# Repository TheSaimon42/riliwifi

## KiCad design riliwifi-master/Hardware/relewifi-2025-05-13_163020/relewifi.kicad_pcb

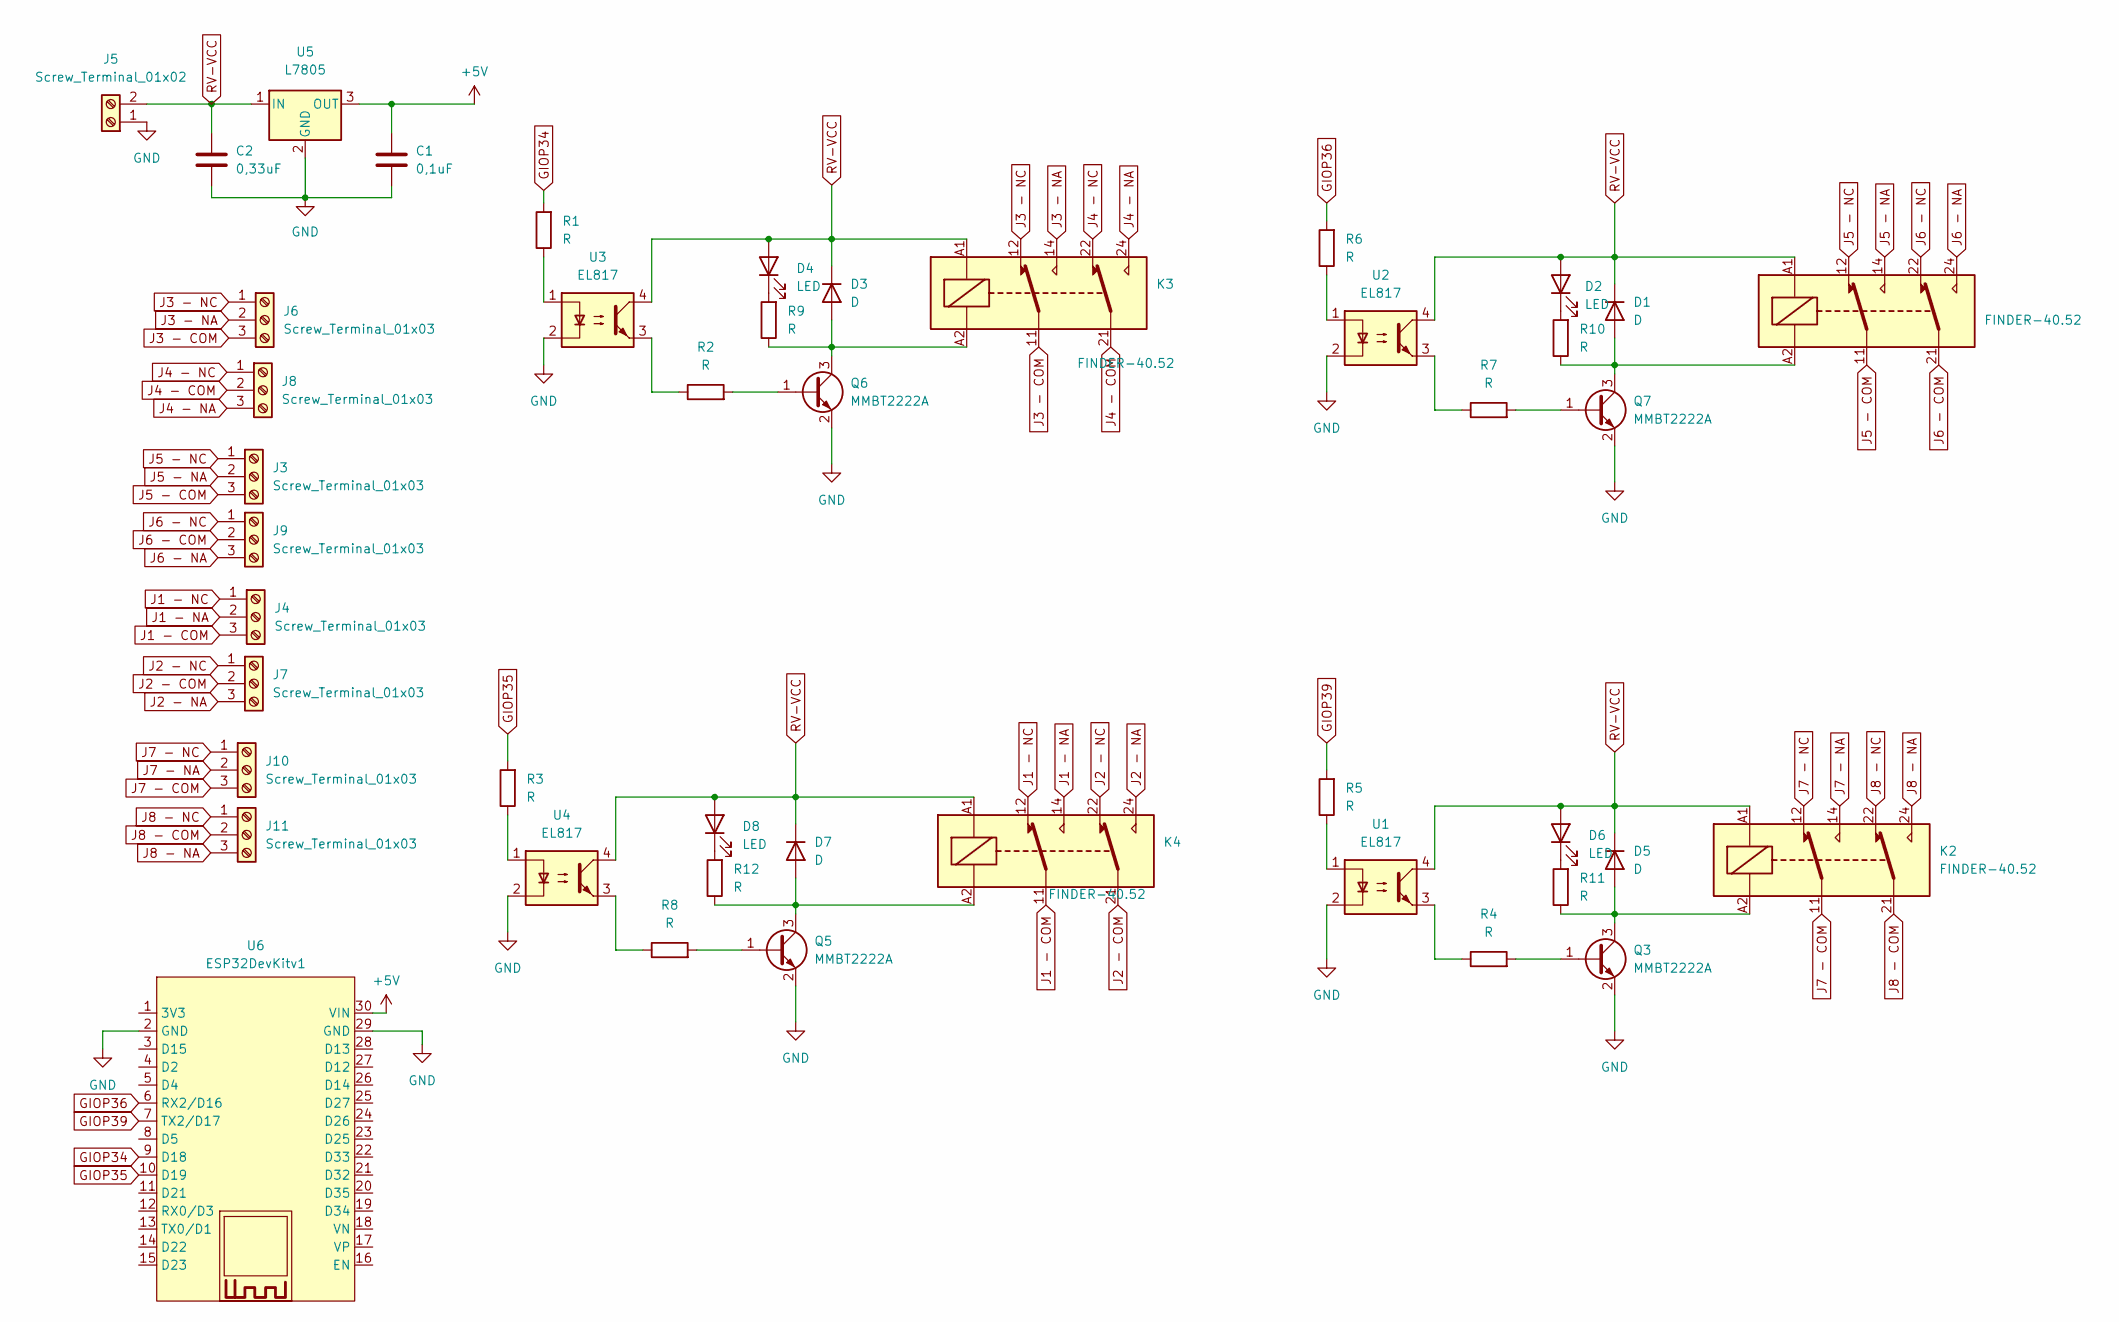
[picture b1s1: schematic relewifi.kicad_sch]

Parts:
C1: 0,1uF; C_Axial_L3.8mm_D2.6mm_P7.50mm_Horizontal
C2: 0,33uF; C_Axial_L3.8mm_D2.6mm_P7.50mm_Horizontal
D1, D3, D5, D7: D; D_SMA
D2, D4, D6, D8: LED; LED_D5.0mm_Clear
J3, J4, J6, J7, J8, J9, J10, J11: Screw_Terminal_01x03; TerminalBlock_Xinya_XY308-2.54-3P_1x03_P2.54mm_Horizontal
J5: Screw_Terminal_01x02; TerminalBlock_bornier-2_P5.08mm
K1, K2, K3, K4: FINDER-40.52; Relay_DPDT_Finder_40.52
Q3, Q5, Q6, Q7: MMBT2222A; SOT-23
R1, R2, R3, R4, R5, R6, R7, R8, R9, R10, R11, R12: R; R_0805_2012Metric
U1, U2, U3, U4: EL817; DIP-4_W7.62mm
U5: L7805; TO-220-3_Vertical
U6: ESP32DevKitv1; ESP32-C3-DevKitM-1

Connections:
+5V: C1.1, U5.3 (OUT), U6.30 (VIN)
GIOP34: R1.2, U6.9 (D18)
GIOP35: R3.2, U6.10 (D19)
GIOP36: R6.2, U6.6 (RX2/D16)
GIOP39: R5.2, U6.7 (TX2/D17)
GND: C1.2, C2.2, J5.1, Q3.2 (E), Q5.2 (E), Q6.2 (E), Q7.2 (E), U1.2, U2.2, U3.2, U4.2, U5.2 (GND), U6.2 (GND), U6.29 (GND)
J1 - COM: J4.3, K4.11
J1 - NA: J4.2, K4.14
J1 - NC: J4.1, K4.12
J2 - COM: J7.2, K4.21
J2 - NA: J7.3, K4.24
J2 - NC: J7.1, K4.22
J3 - COM: J6.3, K3.11
J3 - NA: J6.2, K3.14
J3 - NC: J6.1, K3.12
J4 - COM: J8.2, K3.21
J4 - NA: J8.3, K3.24
J4 - NC: J8.1, K3.22
J5 - COM: J3.3, K1.11
J5 - NA: J3.2, K1.14
J5 - NC: J3.1, K1.12
J6 - COM: J9.2, K1.21
J6 - NA: J9.3, K1.24
J6 - NC: J9.1, K1.22
J7 - COM: J10.3, K2.11
J7 - NA: J10.2, K2.14
J7 - NC: J10.1, K2.12
J8 - COM: J11.2, K2.21
J8 - NA: J11.3, K2.24
J8 - NC: J11.1, K2.22
unnamed: D1.2 (A), K1.A2, Q7.3 (C), R10.1
unnamed: D2.1 (K), R10.2
unnamed: D3.2 (A), K3.A2, Q6.3 (C), R9.1
unnamed: D4.1 (K), R9.2
unnamed: D5.2 (A), K2.A2, Q3.3 (C), R11.1
unnamed: D6.1 (K), R11.2
unnamed: D7.2 (A), K4.A2, Q5.3 (C), R12.1
unnamed: D8.1 (K), R12.2
unnamed: Q3.1 (B), R4.2
unnamed: Q5.1 (B), R8.2
unnamed: Q6.1 (B), R2.2
unnamed: Q7.1 (B), R7.2
unnamed: R1.1, U3.1
unnamed: R2.1, U3.3
unnamed: R3.1, U4.1
unnamed: R4.1, U1.3
unnamed: R5.1, U1.1
unnamed: R6.1, U2.1
unnamed: R7.1, U2.3
unnamed: R8.1, U4.3
RV-VCC: C2.1, D1.1 (K), D2.2 (A), D3.1 (K), D4.2 (A), D5.1 (K), D6.2 (A), D7.1 (K), D8.2 (A), J5.2, K1.A1, K2.A1, K3.A1, K4.A1, U1.4, U2.4, U3.4, U4.4, U5.1 (IN)

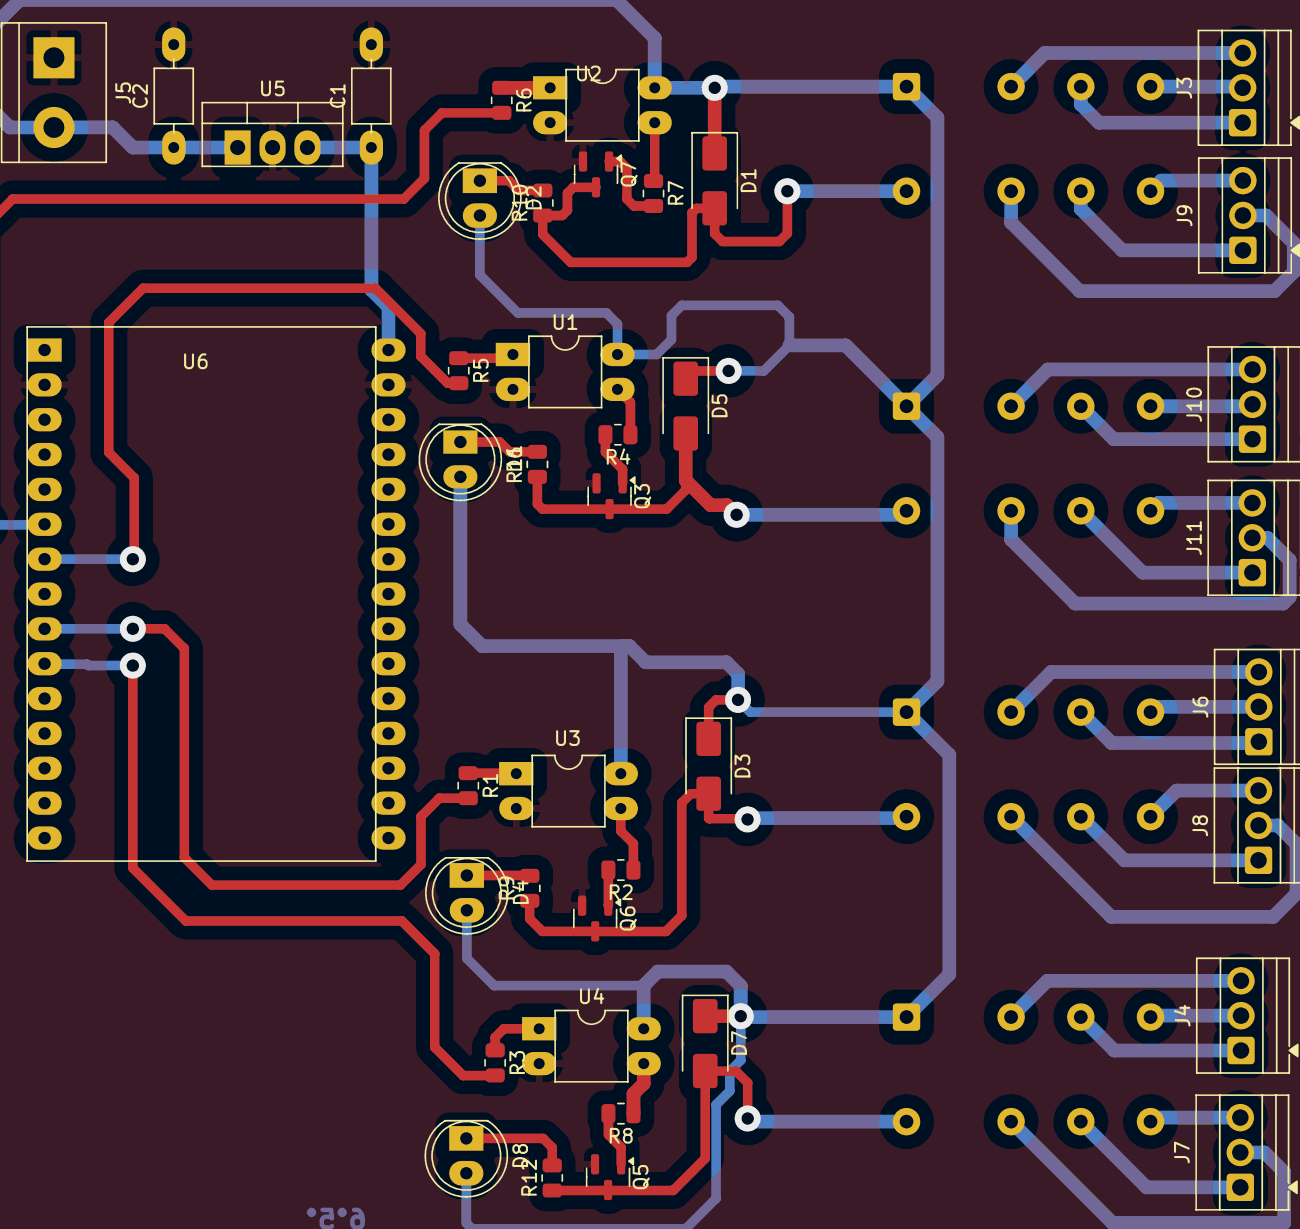
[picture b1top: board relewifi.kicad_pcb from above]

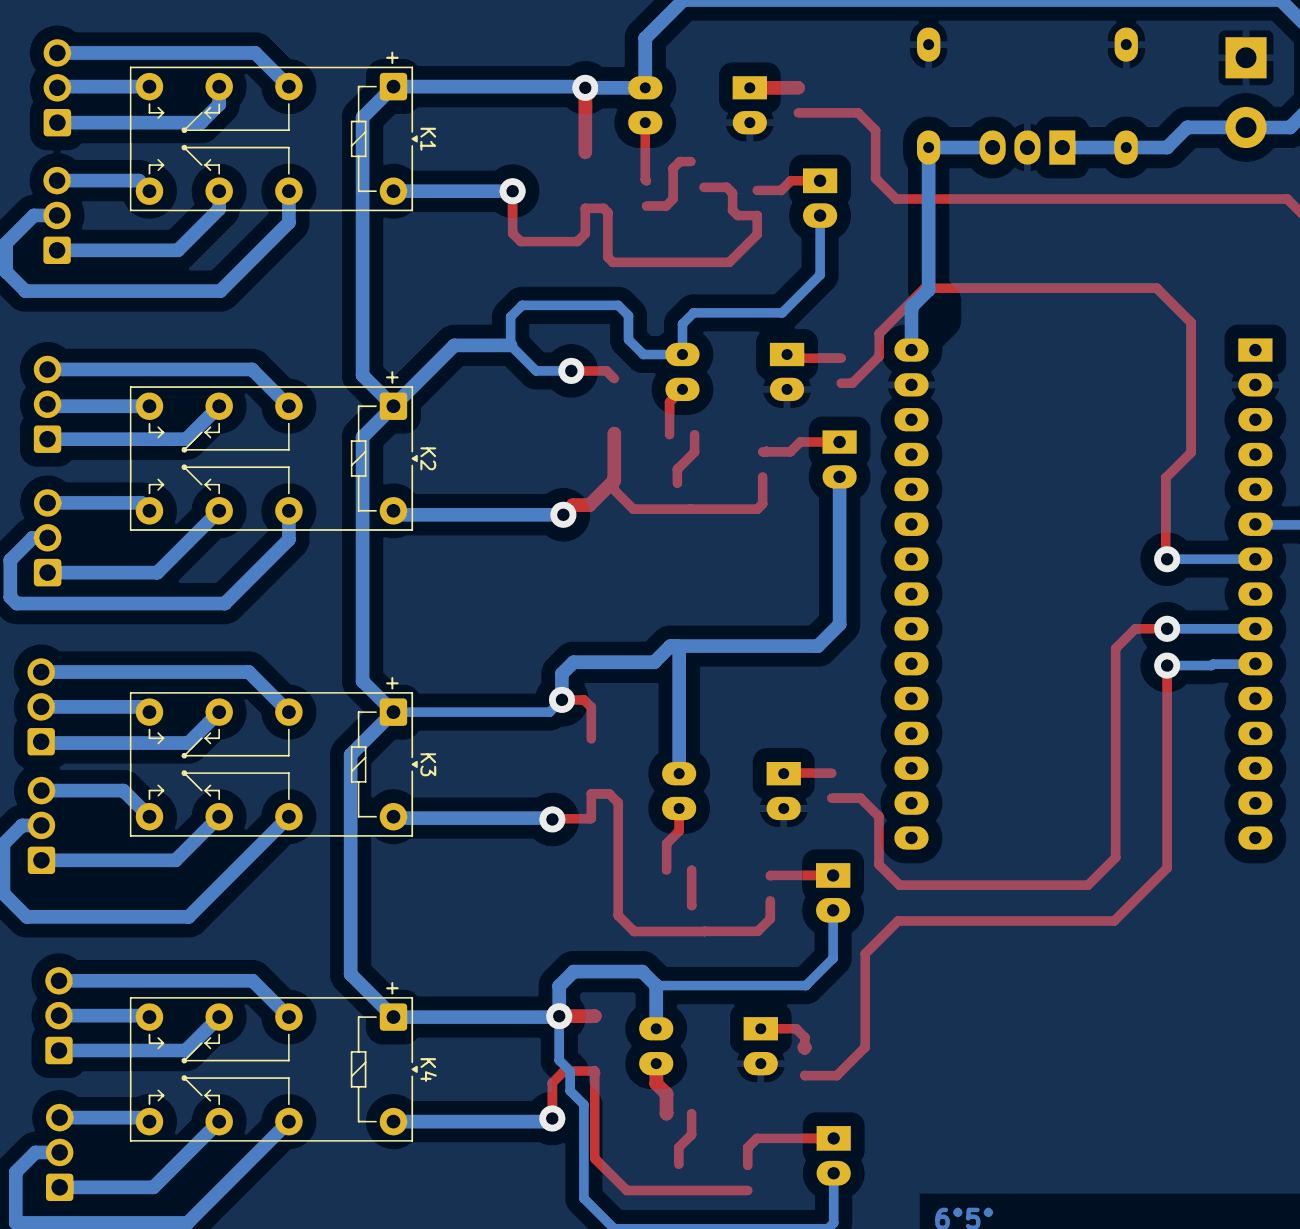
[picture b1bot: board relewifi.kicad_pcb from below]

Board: 2 copper layers, 45 parts (4 on the bottom side), 51 nets.

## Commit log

2025-03-28 Mi primer commit
2025-03-28 modificamos titulo del index.html uwu
2025-03-28 carpetas proyecto añadidas
2025-03-28 Añadimos Proyecto kicad
2025-03-28 Early kicad relay
2025-05-20 avance
2025-05-30 Nuevos Avances
2025-06-06 Avance PCB (6/6/25)
2025-06-06 Ultimo Avance PCB
2025-06-13 Último PCB--Relay WI-FI
2025-06-13 Para imprimir
2025-07-15 esp32 corregido
